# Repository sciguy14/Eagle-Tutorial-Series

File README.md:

Jeremy Blum's Eagle CAD Tutorial Series
=======================================
These files are meant to accompany Jeremy Blum's Eagle CAD Tutorial Series.  
These tutorials were sponsored by element14 (http://www.element14.com) with support from CadSoft (http://www.cadsoftusa.com)  
You can watch these tutorials on youtube or my website:  
>YouTube				- http://www.youtube.com/playlist?list=PL868B73617C6F6FAD  
>Jeremy's Website		- http://jeremyblum.com/category/eagle-tutorials/  

Open Source License
-------------------
These files are distributed under the GNU GPL Open Source License.  
Further information can be found in the LICENSE file.  

Learn More about Eagle
----------------------
If you need help with Eagle or want to learn more, I recommend these resources:  
>element14 CadSoft Group	- http://www.element-14.com/cadsoft  
>Eagle Guided Tour			- http://www.cadsoftusa.com/eagle-pcb-design-software/guided-tour/  
>Sparkfun Eagle Tutorials	- http://www.sparkfun.com/tutorials/108  

Author Info
-----------
The Original author of these files is Jeremy Blum.  
He can be reached through his website, http://www.jeremyblum.com.  
NO WARRANTY is provided with these files, since they are released under the GNU GPL.  
Follow Jeremy on Twitter: http://www.twitter.com/sciguy14  
Subscribe to Jeremy on Youtube: http://www.youtube.com/subscription_center?add_user=sciguy14

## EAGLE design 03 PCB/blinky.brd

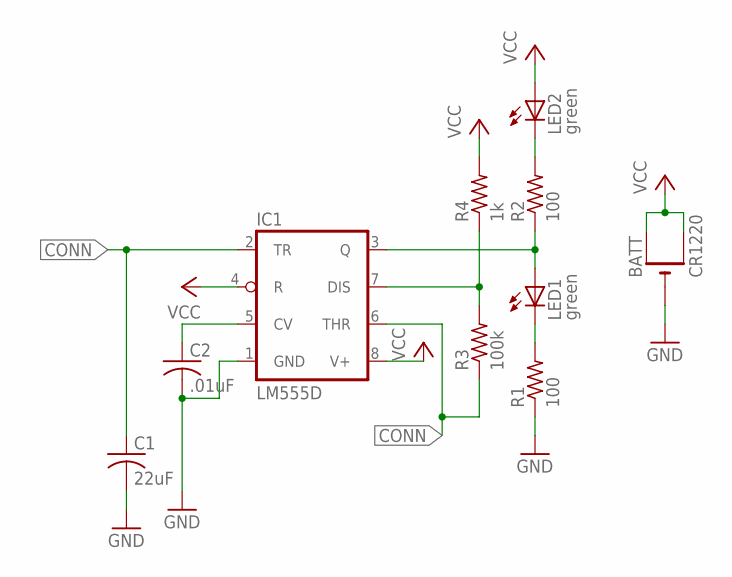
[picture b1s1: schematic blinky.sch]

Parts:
BATT: CR1220; CR1220-SMD; MPN 3080
C1: 22uF; C0805; MPN 08056D226MAT2A
C2: .01uF; C0805; MPN GRM216R71H103KA01D
IC1: LM555D; SO08; MPN TLC555CD.
LED1, LED2: green; CHIPLED_0805; MPN 150080GS75000
R1, R2: 100; R0805; MPN CR0805-JW-101ELF
R3: 100k; R0805; MPN MC 0.1W 0805 5% 100K
R4: 1k; R0805; MPN CRCW08051K00FKTA

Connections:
CONN: C1.1, IC1.2 (TR), IC1.6 (THR), R3.1
GND: BATT.-, C1.2, C2.2, IC1.1 (GND), R1.1
unnamed: LED2.C, R2.2
unnamed: IC1.3 (Q), LED1.A, R2.1
unnamed: LED1.C, R1.2
unnamed: IC1.7 (DIS), R3.2, R4.1
unnamed: C2.1, IC1.5 (CV)
VCC: BATT.+$1 (+), BATT.+$2 (+1), IC1.4 (R), IC1.8 (V+), LED2.A, R4.2

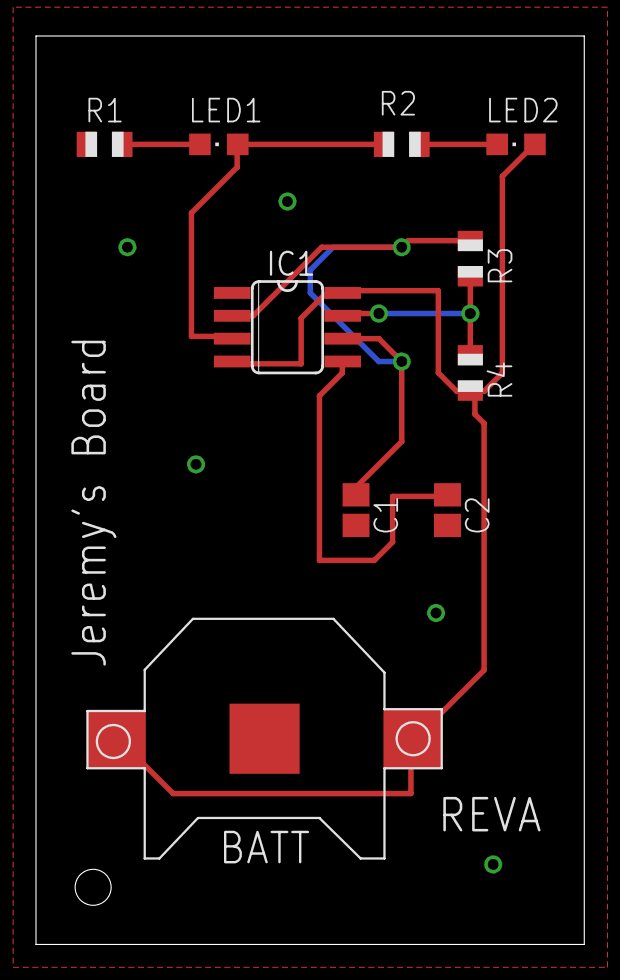
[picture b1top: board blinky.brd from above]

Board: 2 copper layers, 30.5 x 50.5 mm, 10 parts (0 on the bottom side), 8 nets.

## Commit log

2012-06-09 Added Materials for first Tutorial
2012-06-09 Added Schematic Image, updated Readme
2012-06-09 readme update
2012-07-06 Eagle Tutorial 2 Contents Uploaded
2012-07-09 Create gh-pages branch via GitHub
2013-10-10 Added Tutorial 3 design files, CAM template, GERBERS, and text BOM
